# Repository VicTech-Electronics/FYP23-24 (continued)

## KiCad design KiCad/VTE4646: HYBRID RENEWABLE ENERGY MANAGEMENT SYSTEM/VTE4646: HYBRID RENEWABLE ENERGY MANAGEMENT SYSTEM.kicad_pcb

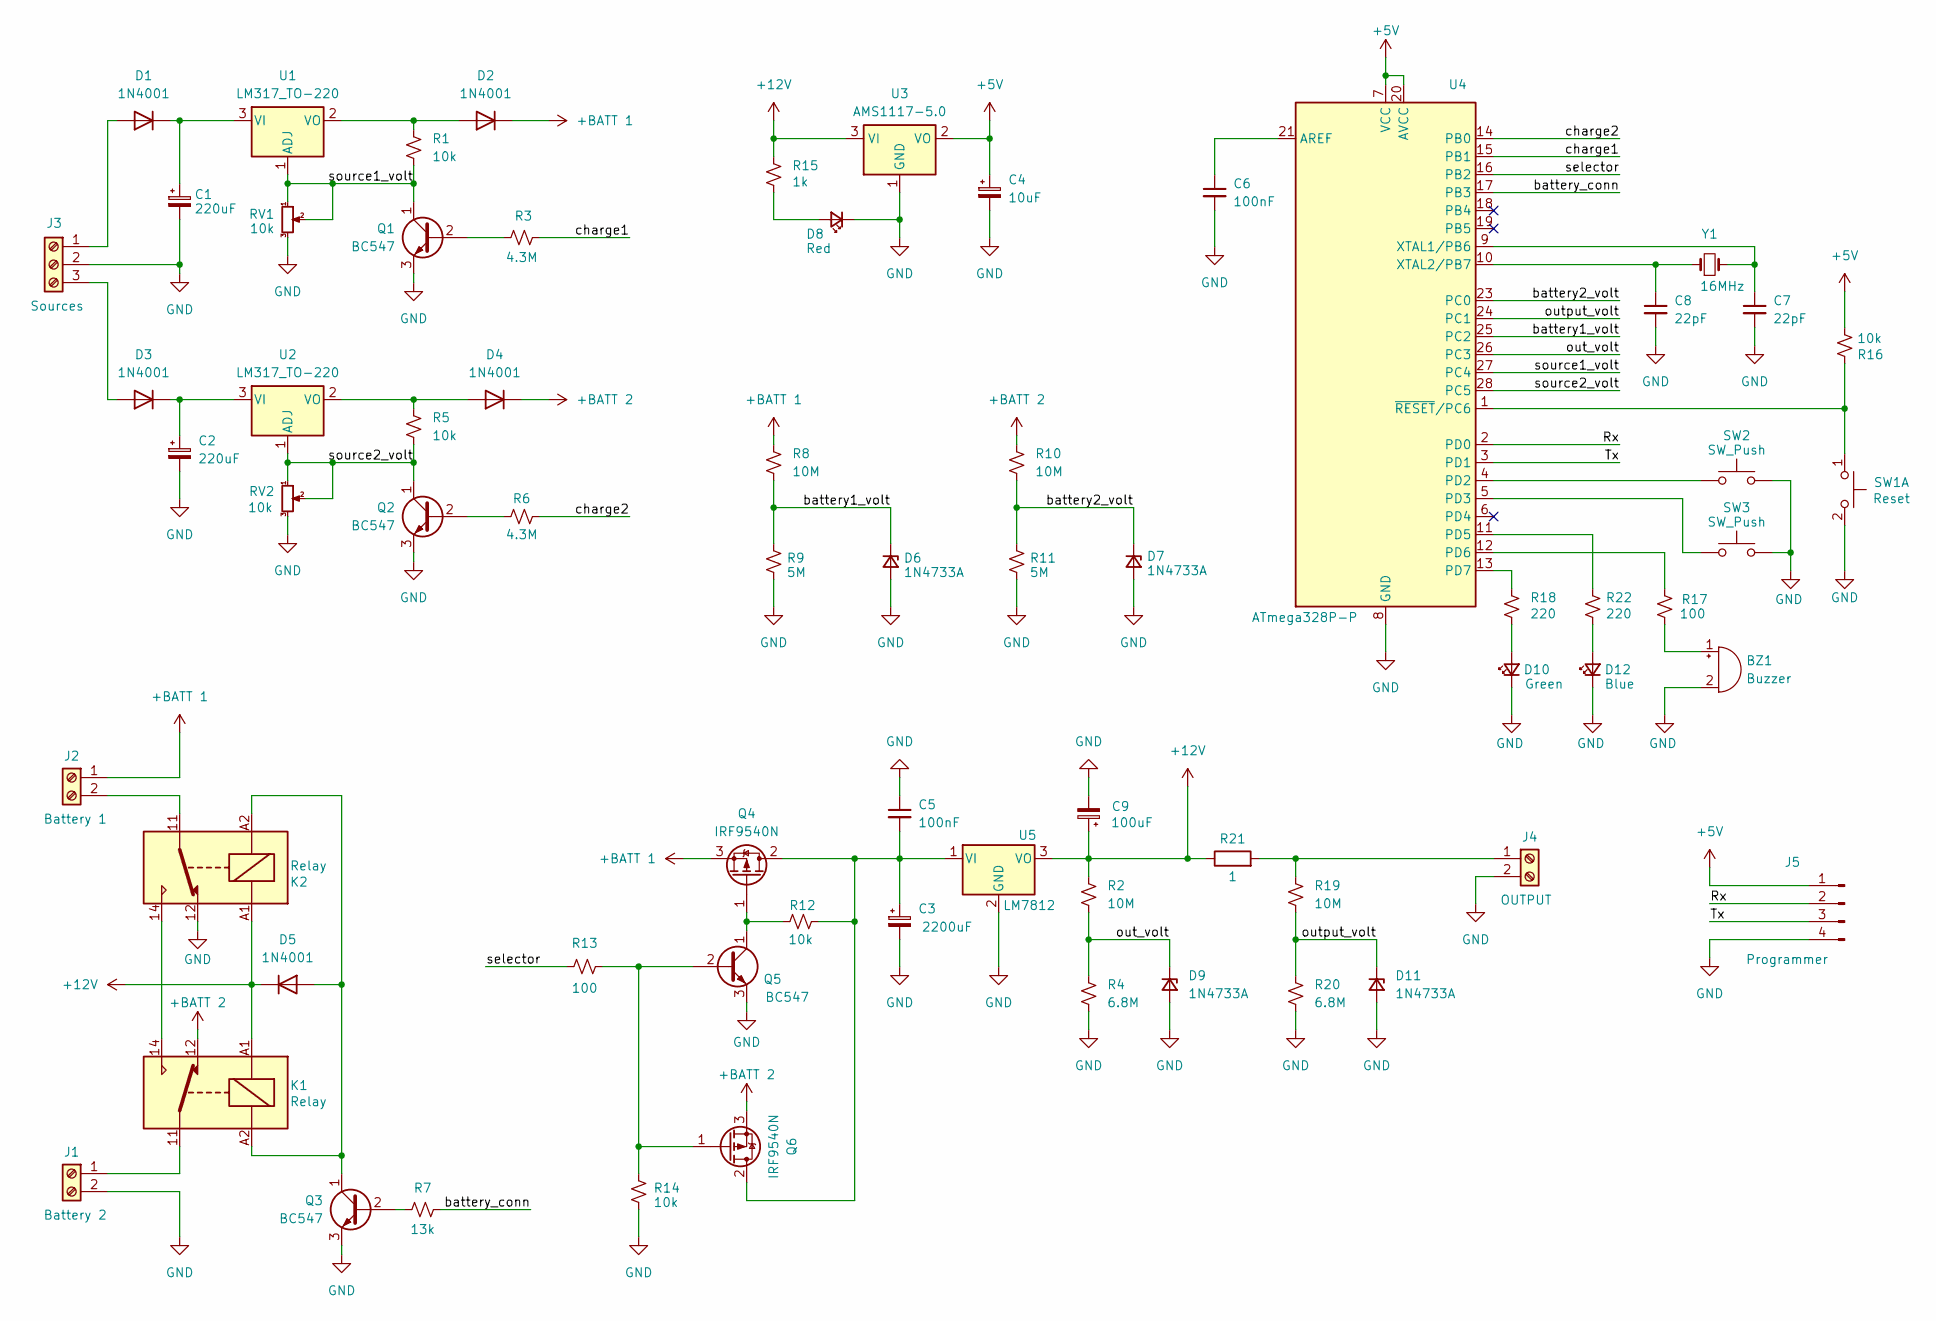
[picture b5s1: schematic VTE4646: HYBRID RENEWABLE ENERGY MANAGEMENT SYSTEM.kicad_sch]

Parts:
BZ1: Buzzer; Buzzer_12x9.5RM7.6
C1, C2: 220uF; CP_Radial_D6.3mm_P2.50mm
C3: 2200uF; CP_Radial_D6.3mm_P2.50mm
C4: 10uF; CP_Radial_D6.3mm_P2.50mm
C5, C6: 100nF; C_Disc_D3.0mm_W1.6mm_P2.50mm
C7, C8: 22pF; C_Disc_D3.0mm_W1.6mm_P2.50mm
C9: 100uF; CP_Radial_D6.3mm_P2.50mm
D1, D2, D3, D4, D5: 1N4001; D_DO-41_SOD81_P10.16mm_Horizontal
D6, D7, D9, D11: 1N4733A; D_A-405_P10.16mm_Horizontal
D8: Red; LED_D3.0mm_Clear
D10: Green; LED_D3.0mm_Clear
D12: Blue; LED_D3.0mm_Clear
J1: Battery 2; TerminalBlock_bornier-2_P5.08mm
J2: Battery 1; TerminalBlock_bornier-2_P5.08mm
J3: Sources; TerminalBlock_bornier-3_P5.08mm
J4: OUTPUT; TerminalBlock_bornier-2_P5.08mm
J5: Programmer; PinHeader_1x04_P2.54mm_Vertical
K1, K2: Relay; Relay_SPDT_Finder_36.11
Q1, Q2, Q3, Q5: BC547; TO-92_Inline
Q4, Q6: IRF9540N; TO-220-3_Vertical
R1, R5, R12, R14, R16: 10k; R_Axial_DIN0207_L6.3mm_D2.5mm_P10.16mm_Horizontal
R2, R8, R10, R19: 10M; R_Axial_DIN0207_L6.3mm_D2.5mm_P10.16mm_Horizontal
R3, R6: 4.3M; R_Axial_DIN0207_L6.3mm_D2.5mm_P10.16mm_Horizontal
R4, R20: 6.8M; R_Axial_DIN0207_L6.3mm_D2.5mm_P10.16mm_Horizontal
R7: 13k; R_Axial_DIN0207_L6.3mm_D2.5mm_P10.16mm_Horizontal
R9, R11: 5M; R_Axial_DIN0207_L6.3mm_D2.5mm_P10.16mm_Horizontal
R13, R17: 100; R_Axial_DIN0207_L6.3mm_D2.5mm_P10.16mm_Horizontal
R15: 1k; R_Axial_DIN0207_L6.3mm_D2.5mm_P10.16mm_Horizontal
R18, R22: 220; R_Axial_DIN0207_L6.3mm_D2.5mm_P10.16mm_Horizontal
R21: 1; R_Axial_Power_L20.0mm_W6.4mm_P30.48mm
RV1, RV2: 10k; Potentiometer_Runtron_RM-065_Vertical
SW1: Reset; SW_PUSH_6mm_H4.3mm
SW2, SW3: SW_Push; PinHeader_2x01_P2.00mm_Vertical
U1, U2: LM317_TO-220; TO-220-3_Vertical
U3: AMS1117-5.0; SOT-223-3_TabPin2
U4: ATmega328P-P; DIP-28_W7.62mm
U5: LM7812; TO-220-3_Vertical
Y1: 16MHz; Crystal_HC18-U_Vertical

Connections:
+5V: C4.1, J5.1, R16.2, U3.2 (VO), U4.7 (VCC), U4.20 (AVCC)
+12V: C9.1, D5.1 (K), K1.A1, K2.A1, R2.1, R15.1, R21.1, U3.3 (VI), U5.3 (VO)
+BATT 1: D2.1 (K), J2.1, Q4.3 (S), R8.1
+BATT 2: D4.1 (K), K1.12, Q6.3 (S), R10.1
/Rx: J5.2, U4.2 (PD0)
/Tx: J5.3, U4.3 (PD1)
/battery1_volt: D6.1 (K), R8.2, R9.1, U4.25 (PC2)
/battery2_volt: D7.1 (K), R10.2, R11.1, U4.23 (PC0)
/battery_conn: R7.2, U4.17 (PB3)
/charge1: R3.2, U4.15 (PB1)
/charge2: R6.2, U4.14 (PB0)
/out_volt: D9.1 (K), R2.2, R4.1, U4.26 (PC3)
/output_volt: D11.1 (K), R19.2, R20.1, U4.24 (PC1)
/selector: R13.1, U4.16 (PB2)
/source1_volt: Q1.1 (C), R1.2, RV1.1, RV1.2, U1.1 (ADJ), U4.27 (PC4)
/source2_volt: Q2.1 (C), R5.2, RV2.1, RV2.2, U2.1 (ADJ), U4.28 (PC5)
GND: BZ1.2 (-), C1.2, C2.2, C3.2, C4.2, C5.1, C6.2, C7.2, C8.2, C9.2, D6.2 (A), D7.2 (A), D8.1 (K), D9.2 (A), D10.1 (K), D11.2 (A), D12.1 (K), J1.2, J3.2, J4.2, J5.4, K2.12, Q1.3 (E), Q2.3 (E), Q3.3 (E), Q5.3 (E), R4.2, R9.2, R11.2, R14.2, R20.2, RV1.3, RV2.3, SW1.2 (D), SW2.2, SW3.2, U3.1 (GND), U4.8 (GND), U4.22 (GND), U5.2 (GND)
unnamed: BZ1.1 (+), R17.2
unnamed: D1.2 (A), J3.1
unnamed: C1.1, D1.1 (K), U1.3 (VI)
unnamed: D2.2 (A), R1.1, U1.2 (VO)
unnamed: D3.2 (A), J3.3
unnamed: C2.1, D3.1 (K), U2.3 (VI)
unnamed: D4.2 (A), R5.1, U2.2 (VO)
unnamed: D5.2 (A), K1.A2, K2.A2, Q3.1 (C)
unnamed: D8.2 (A), R15.2
unnamed: D10.2 (A), R18.2
unnamed: D12.2 (A), R22.2
unnamed: J1.1, K1.11
unnamed: J2.2, K2.11
unnamed: J4.1, R19.1, R21.2
unnamed: K1.14, K2.14
unnamed: Q1.2 (B), R3.1
unnamed: Q2.2 (B), R6.1
unnamed: Q3.2 (B), R7.1
unnamed: C3.1, C5.2, Q4.2 (D), Q6.2 (D), R12.2, U5.1 (VI)
unnamed: Q4.1 (G), Q5.1 (C), R12.1
unnamed: Q5.2 (B), Q6.1 (G), R13.2, R14.1
unnamed: R16.1, SW1.1 (C), U4.1 (~RESET/PC6)
unnamed: C6.1, U4.21 (AREF)
unnamed: SW2.1, U4.4 (PD2)
unnamed: SW3.1, U4.5 (PD3)
unnamed: R22.1, U4.11 (PD5)
unnamed: R17.1, U4.12 (PD6)
unnamed: R18.1, U4.13 (PD7)
unnamed: C7.1, U4.9 (XTAL1/PB6), Y1.2
unnamed: C8.1, U4.10 (XTAL2/PB7), Y1.1

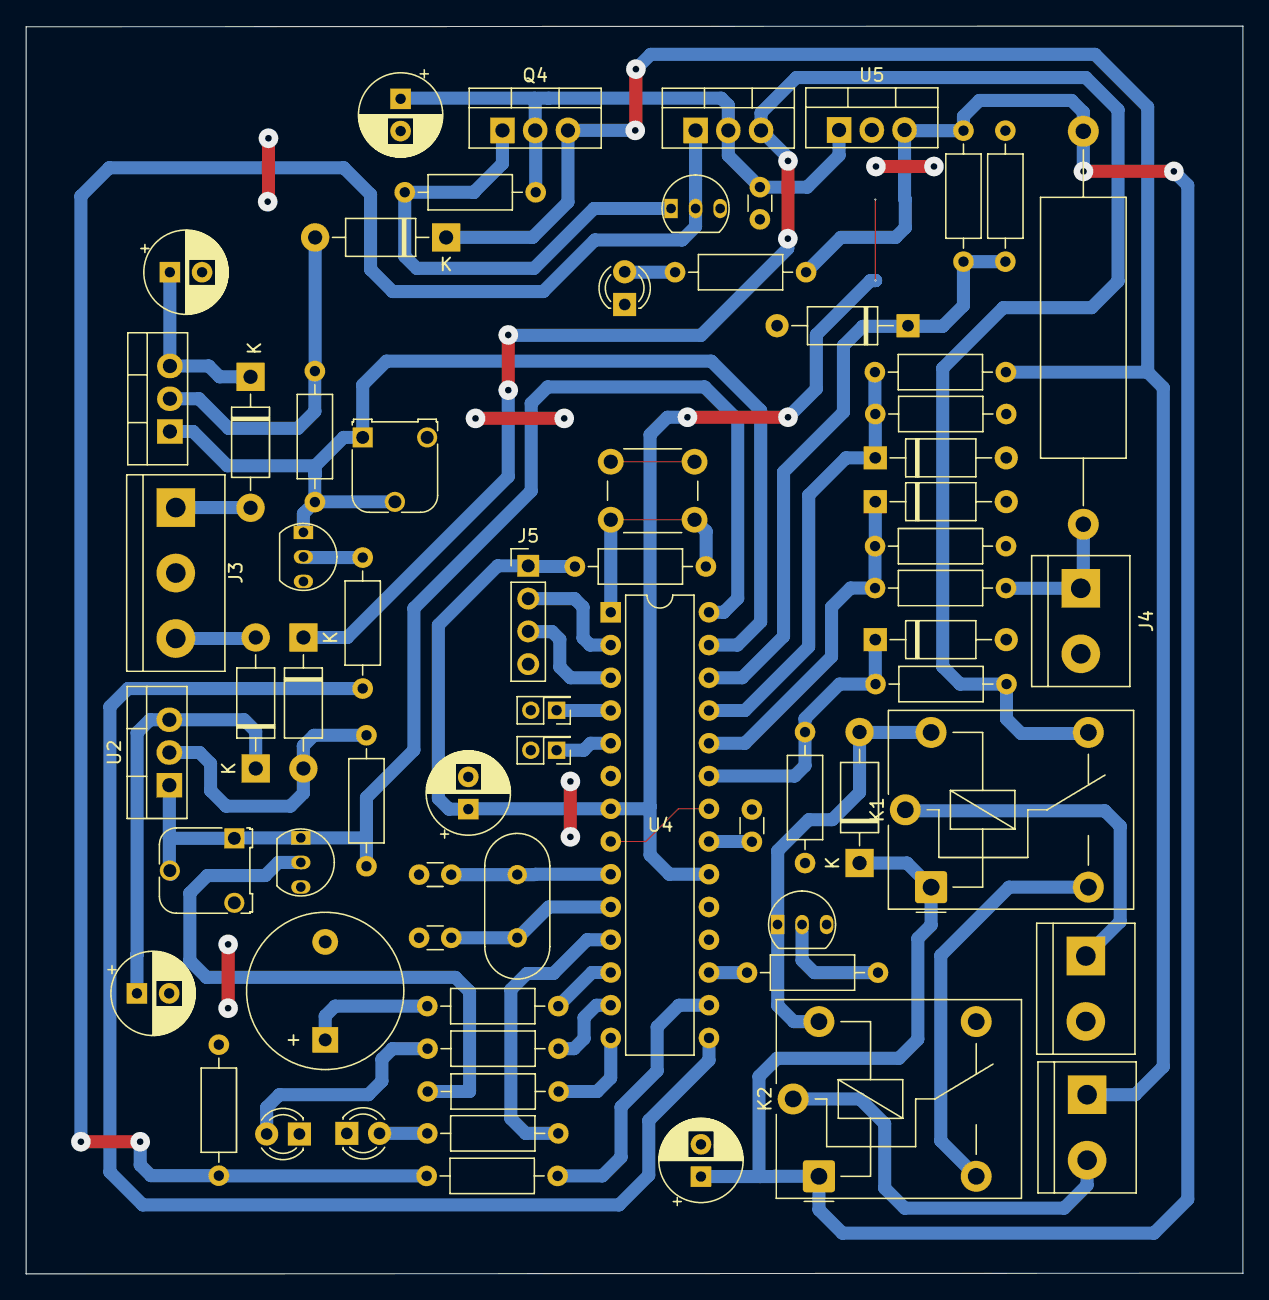
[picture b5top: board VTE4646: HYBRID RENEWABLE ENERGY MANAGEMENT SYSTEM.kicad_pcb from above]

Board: 2 copper layers, 94.4 x 96.8 mm, 68 parts (1 on the bottom side), 47 nets.

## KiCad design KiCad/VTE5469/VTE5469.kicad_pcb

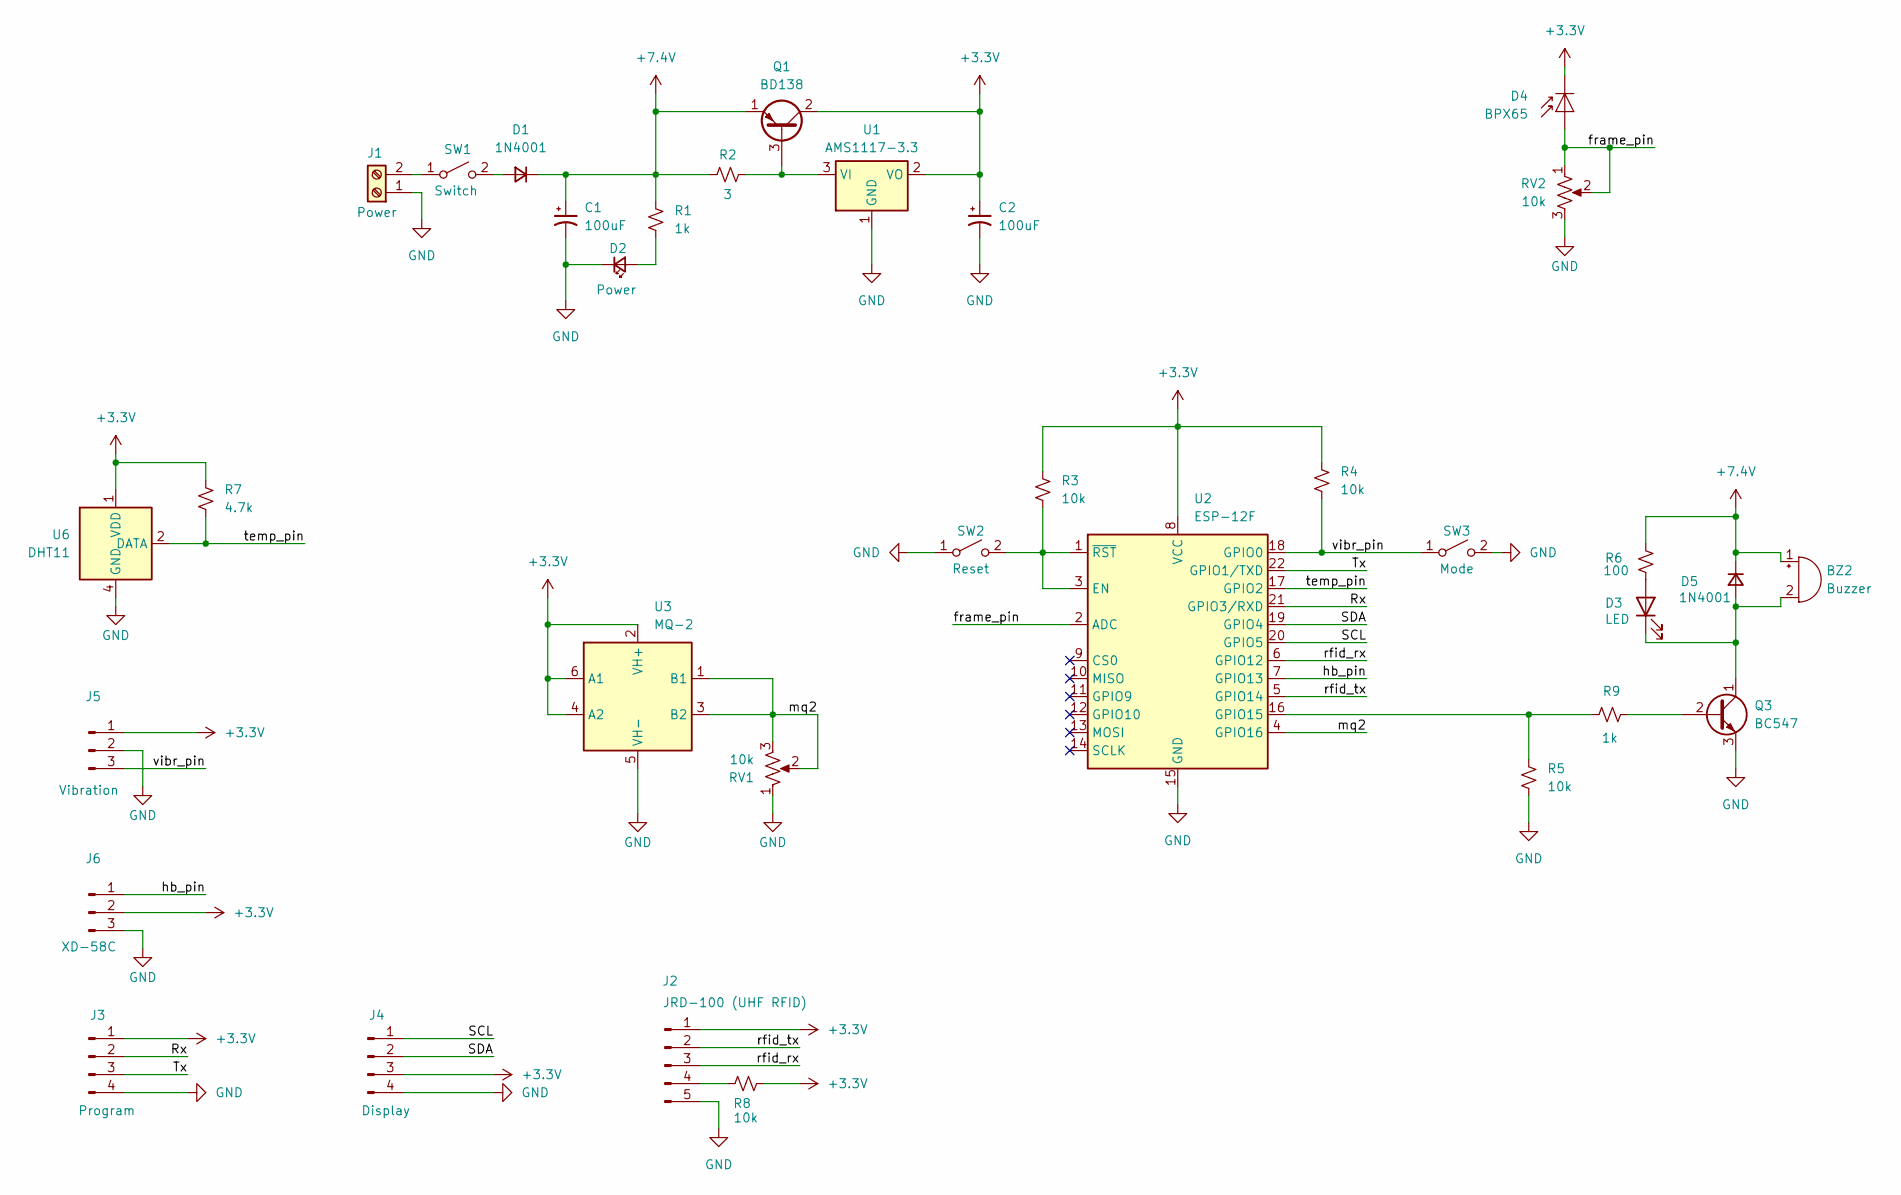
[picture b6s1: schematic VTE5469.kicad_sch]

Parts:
BZ2: Buzzer; PinHeader_1x02_P2.54mm_Vertical
C1, C2: 100uF; CP_Radial_D5.0mm_P2.50mm
D1, D5: 1N4001; D_A-405_P10.16mm_Horizontal
D2: Power; LED_D3.0mm
D3: LED; LED_D3.0mm
D4: BPX65; TO-18-2_Lens
J1: Power; TerminalBlock_bornier-2_P5.08mm
J2: JRD-100 (UHF RFID); PinHeader_1x05_P2.54mm_Vertical
J3: Program; PinHeader_1x04_P2.54mm_Vertical
J4: Display; PinHeader_1x04_P2.54mm_Vertical
J5: Vibration; PinHeader_1x03_P2.54mm_Vertical
J6: XD-58C; PinHeader_1x03_P2.54mm_Vertical
Q1: BD138; TO-126-3_Vertical
Q3: BC547; TO-92_Inline
R1, R9: 1k; R_Axial_DIN0207_L6.3mm_D2.5mm_P10.16mm_Horizontal
R2: 3; R_Axial_DIN0207_L6.3mm_D2.5mm_P10.16mm_Horizontal
R3, R4, R5, R8: 10k; R_Axial_DIN0207_L6.3mm_D2.5mm_P10.16mm_Horizontal
R6: 100; R_Axial_DIN0207_L6.3mm_D2.5mm_P10.16mm_Horizontal
R7: 4.7k; R_Axial_DIN0207_L6.3mm_D2.5mm_P10.16mm_Horizontal
RV1, RV2: 10k; Potentiometer_Runtron_RM-065_Vertical
SW1: Switch; TestPoint_2Pads_Pitch2.54mm_Drill0.8mm
SW2: Reset; SW_PUSH_6mm
SW3: Mode; SW_PUSH_6mm
U1: AMS1117-3.3; SOT-223-3_TabPin2
U2: ESP-12F; ESP-12E
U3: MQ-2; MQ-6
U6: DHT11; Aosong_DHT11_5.5x12.0_P2.54mm

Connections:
+3.3V: C2.1, D4.1 (K), J2.1, J3.1, J4.3, J5.1, J6.2, Q1.2 (C), R3.1, R4.1, R7.1, R8.2, U1.2 (VO), U2.8 (VCC), U3.2 (VH+), U3.4 (A2), U3.6 (A1), U6.1 (VDD)
+7.4V: BZ2.1 (+), C1.1, D1.1 (K), D5.1 (K), Q1.1 (E), R1.1, R2.1, R6.1
/Rx: J3.2, U2.21 (GPIO3/RXD)
/SCL: J4.1, U2.20 (GPIO5)
/SDA: J4.2, U2.19 (GPIO4)
/Tx: J3.3, U2.22 (GPIO1/TXD)
/frame_pin: D4.2 (A), RV2.1, RV2.2, U2.2 (ADC)
/hb_pin: J6.1, U2.7 (GPIO13)
/mq2: RV1.2, RV1.3, U2.4 (GPIO16), U3.1 (B1), U3.3 (B2)
/rfid_rx: J2.3, U2.6 (GPIO12)
/rfid_tx: J2.2, U2.5 (GPIO14)
/temp_pin: R7.2, U2.17 (GPIO2), U6.2 (DATA)
/vibr_pin: J5.3, R4.2, SW3.1 (A), U2.18 (GPIO0)
GND: C1.2, C2.2, D2.1 (K), J1.1, J2.5, J3.4, J4.4, J5.2, J6.3, Q3.3 (E), R5.2, RV1.1, RV2.3, SW2.1 (A), SW3.2 (B), U1.1 (GND), U2.15 (GND), U3.5 (VH-), U6.4 (GND)
unnamed: BZ2.2 (-), D3.1 (K), D5.2 (A), Q3.1 (C)
unnamed: D1.2 (A), SW1.2 (B)
unnamed: D2.2 (A), R1.2
unnamed: D3.2 (A), R6.2
unnamed: J1.2, SW1.1 (A)
unnamed: J2.4, R8.1
unnamed: Q1.3 (B), R2.2, U1.3 (VI)
unnamed: Q3.2 (B), R9.2
unnamed: R3.2, SW2.2 (B), U2.1 (~RST), U2.3 (EN)
unnamed: R5.1, R9.1, U2.16 (GPIO15)

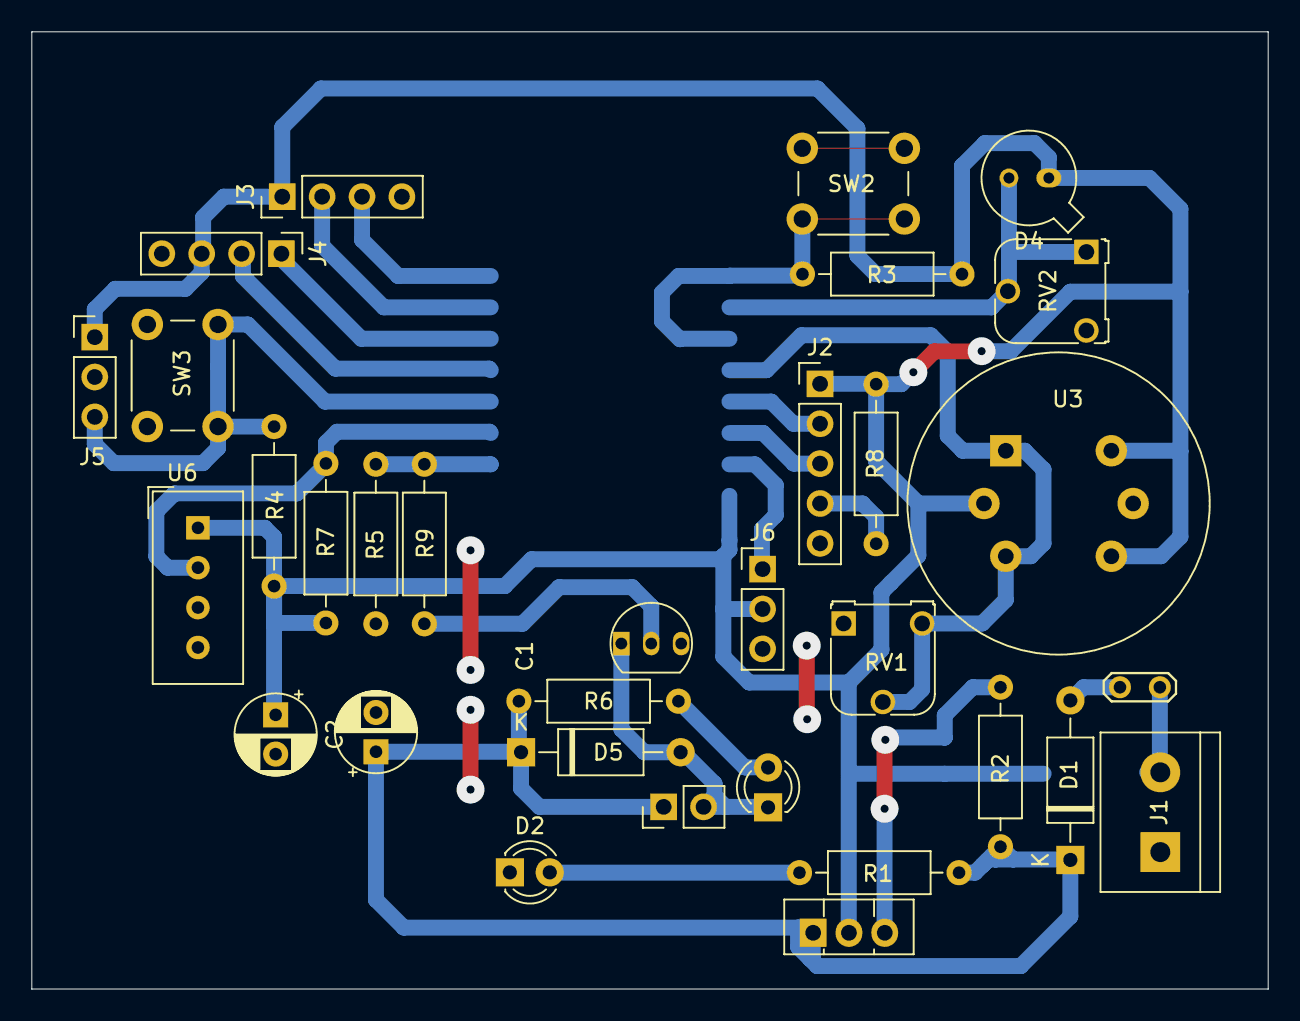
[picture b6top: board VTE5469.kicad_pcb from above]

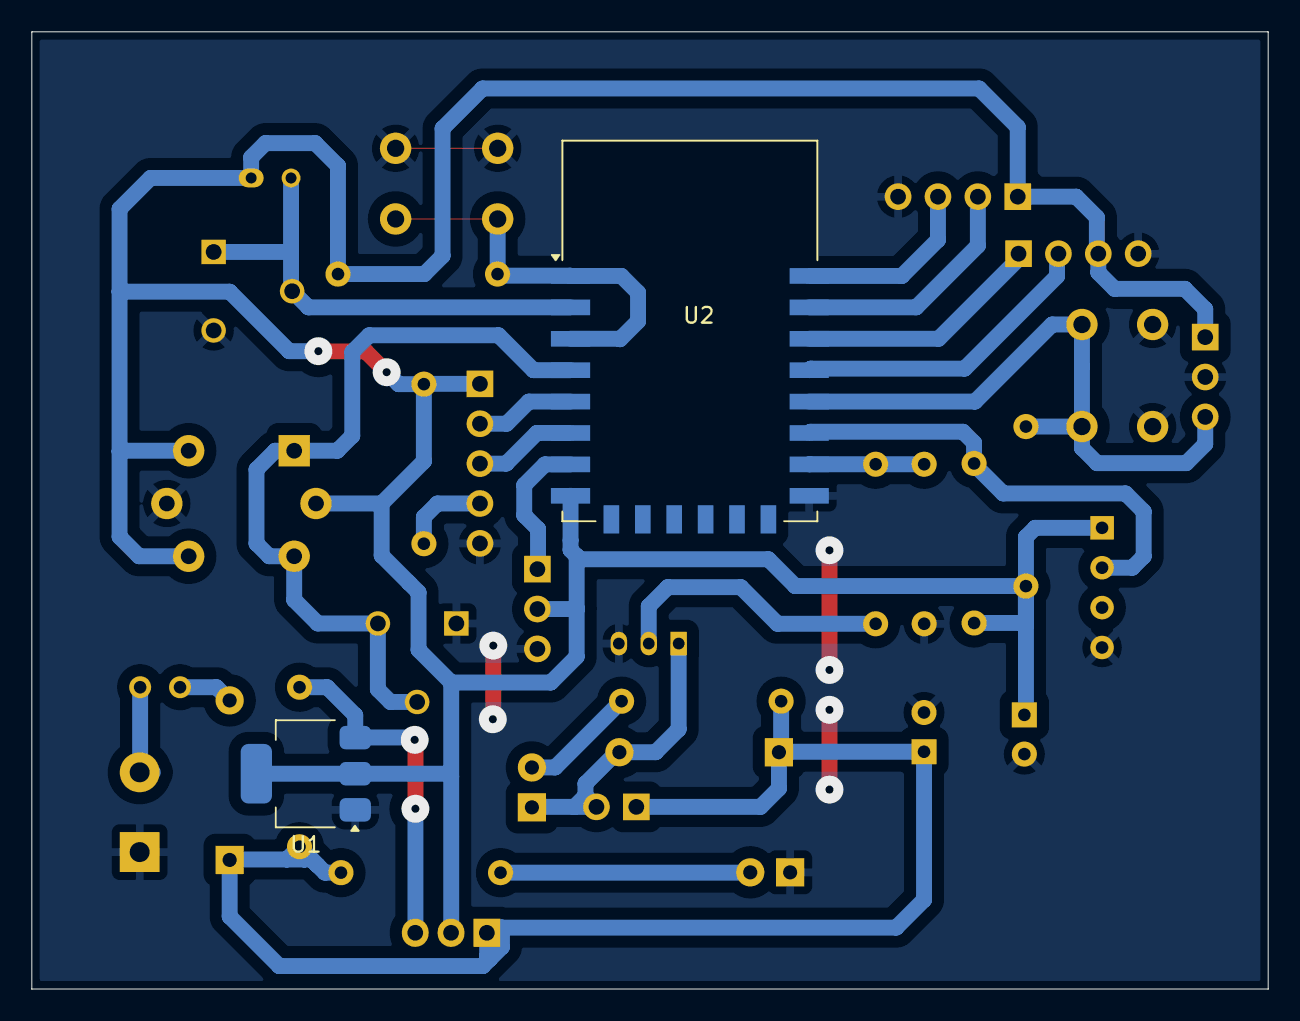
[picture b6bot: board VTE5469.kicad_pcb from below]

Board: 2 copper layers, 78.7 x 61.0 mm, 34 parts (2 on the bottom side), 24 nets.

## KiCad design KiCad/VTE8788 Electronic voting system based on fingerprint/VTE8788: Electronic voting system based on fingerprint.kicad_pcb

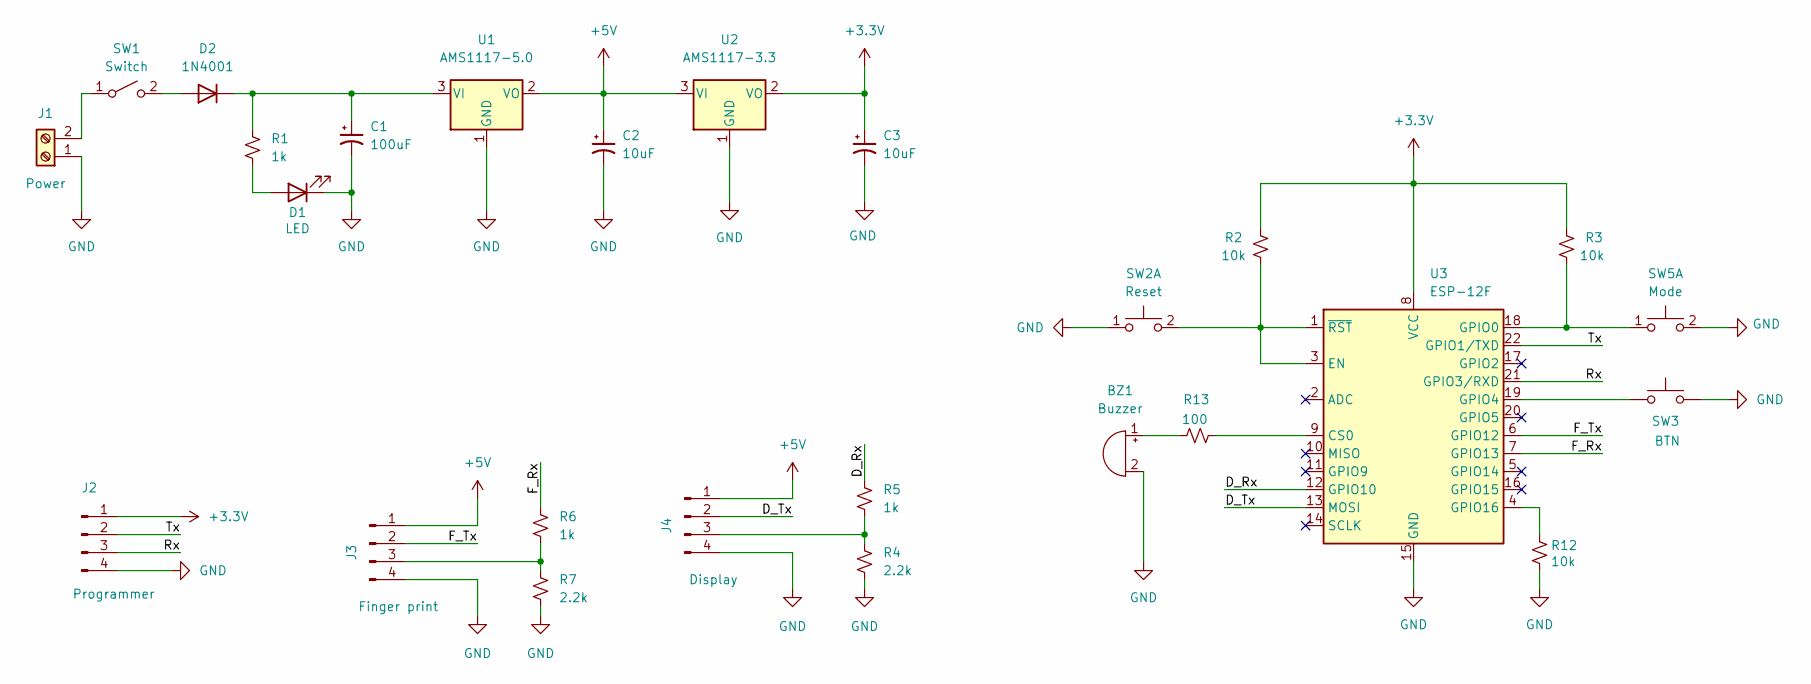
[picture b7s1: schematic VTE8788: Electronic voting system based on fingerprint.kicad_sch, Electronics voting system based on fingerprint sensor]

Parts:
BZ1: Buzzer; Buzzer_12x9.5RM7.6
C1: 100uF; CP_Radial_D4.0mm_P2.00mm
C2, C3: 10uF; CP_Radial_D4.0mm_P2.00mm
D1: LED; LED_D3.0mm
D2: 1N4001; D_DO-41_SOD81_P10.16mm_Horizontal
J1: Power; TerminalBlock_bornier-2_P5.08mm
J2: Programmer; PinHeader_1x04_P2.54mm_Vertical
J3: Finger print; PinHeader_1x04_P2.54mm_Vertical
J4: Display; PinHeader_1x04_P2.54mm_Vertical
R1, R5, R6: 1k; R_Axial_DIN0207_L6.3mm_D2.5mm_P10.16mm_Horizontal
R2, R3, R12: 10k; R_Axial_DIN0207_L6.3mm_D2.5mm_P10.16mm_Horizontal
R4, R7: 2.2k; R_Axial_DIN0207_L6.3mm_D2.5mm_P10.16mm_Horizontal
R13: 100; R_Axial_DIN0207_L6.3mm_D2.5mm_P10.16mm_Horizontal
SW1: Switch; TestPoint_2Pads_Pitch2.54mm_Drill0.8mm
SW2: Reset; SW_PUSH_6mm
SW3: BTN; TestPoint_2Pads_Pitch2.54mm_Drill0.8mm
SW5: Mode; SW_PUSH_6mm
U1: AMS1117-5.0; SOT-223-3_TabPin2
U2: AMS1117-3.3; SOT-223-3_TabPin2
U3: ESP-12F; ESP-12E

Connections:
+3.3V: C3.1, J2.1, R2.2, R3.1, U2.2 (VO), U3.8 (VCC)
+5V: C2.1, J3.1, J4.1, U1.2 (VO), U2.3 (VI)
/D_Rx: R5.1, U3.12 (GPIO10)
/D_Tx: J4.2, U3.13 (MOSI)
/F_Rx: R6.1, U3.7 (GPIO13)
/F_Tx: J3.2, U3.6 (GPIO12)
/Rx: J2.3, U3.21 (GPIO3/RXD)
/Tx: J2.2, U3.22 (GPIO1/TXD)
GND: BZ1.2 (+), C1.2, C2.2, C3.2, D1.1 (K), J1.1, J2.4, J3.4, J4.4, R4.2, R7.2, R12.2, SW2.1 (C), SW3.2, SW5.2 (D), U1.1 (GND), U2.1 (GND), U3.15 (GND)
unnamed: BZ1.1 (-), R13.1
unnamed: D1.2 (A), R1.2
unnamed: D2.2 (A), SW1.2 (B)
unnamed: C1.1, D2.1 (K), R1.1, U1.3 (VI)
unnamed: J1.2, SW1.1 (A)
unnamed: J3.3, R6.2, R7.1
unnamed: J4.3, R4.1, R5.2
unnamed: R2.1, SW2.2 (D), U3.1 (~RST), U3.3 (EN)
unnamed: R3.2, SW5.1 (C), U3.18 (GPIO0)
unnamed: R13.2, U3.9 (CS0)
unnamed: SW3.1, U3.19 (GPIO4)
unnamed: R12.1, U3.4 (GPIO16)

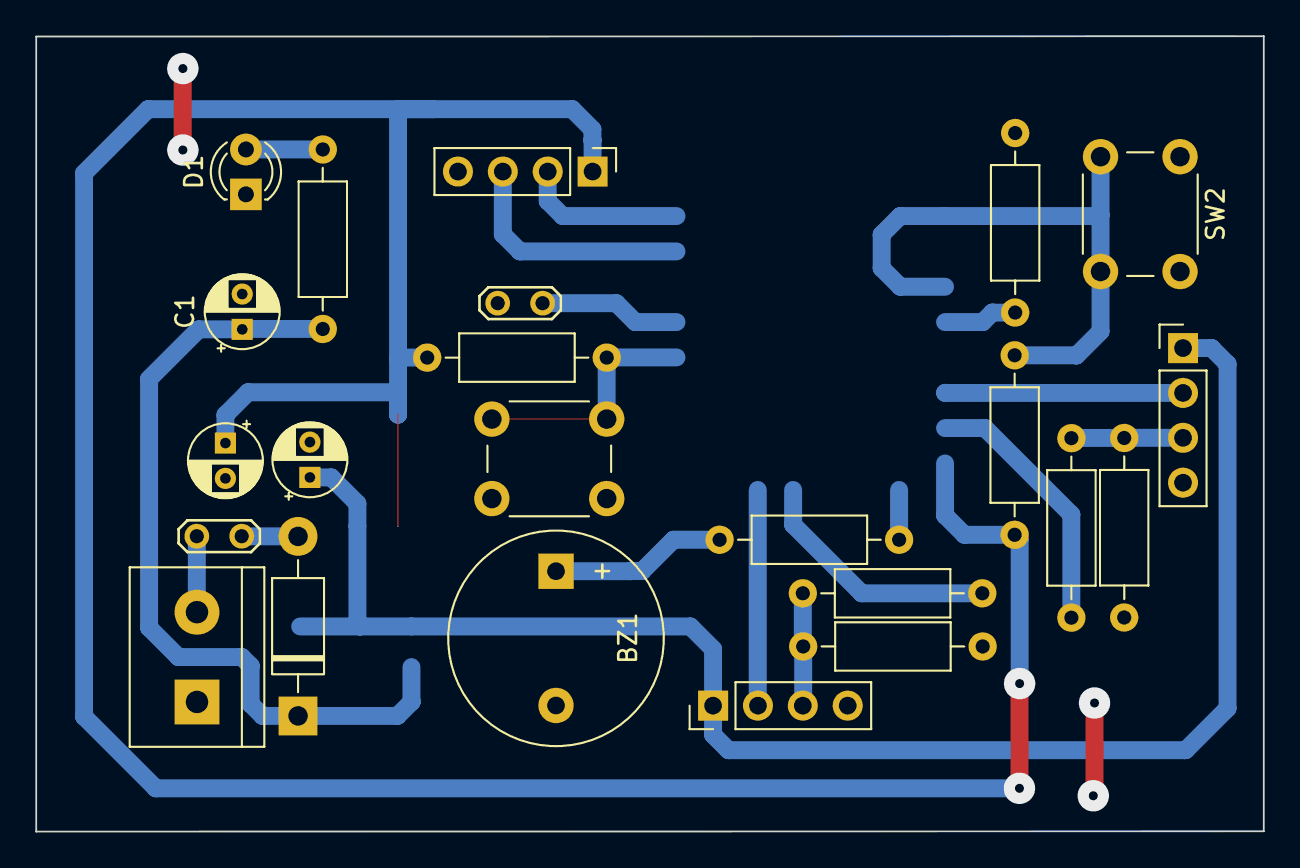
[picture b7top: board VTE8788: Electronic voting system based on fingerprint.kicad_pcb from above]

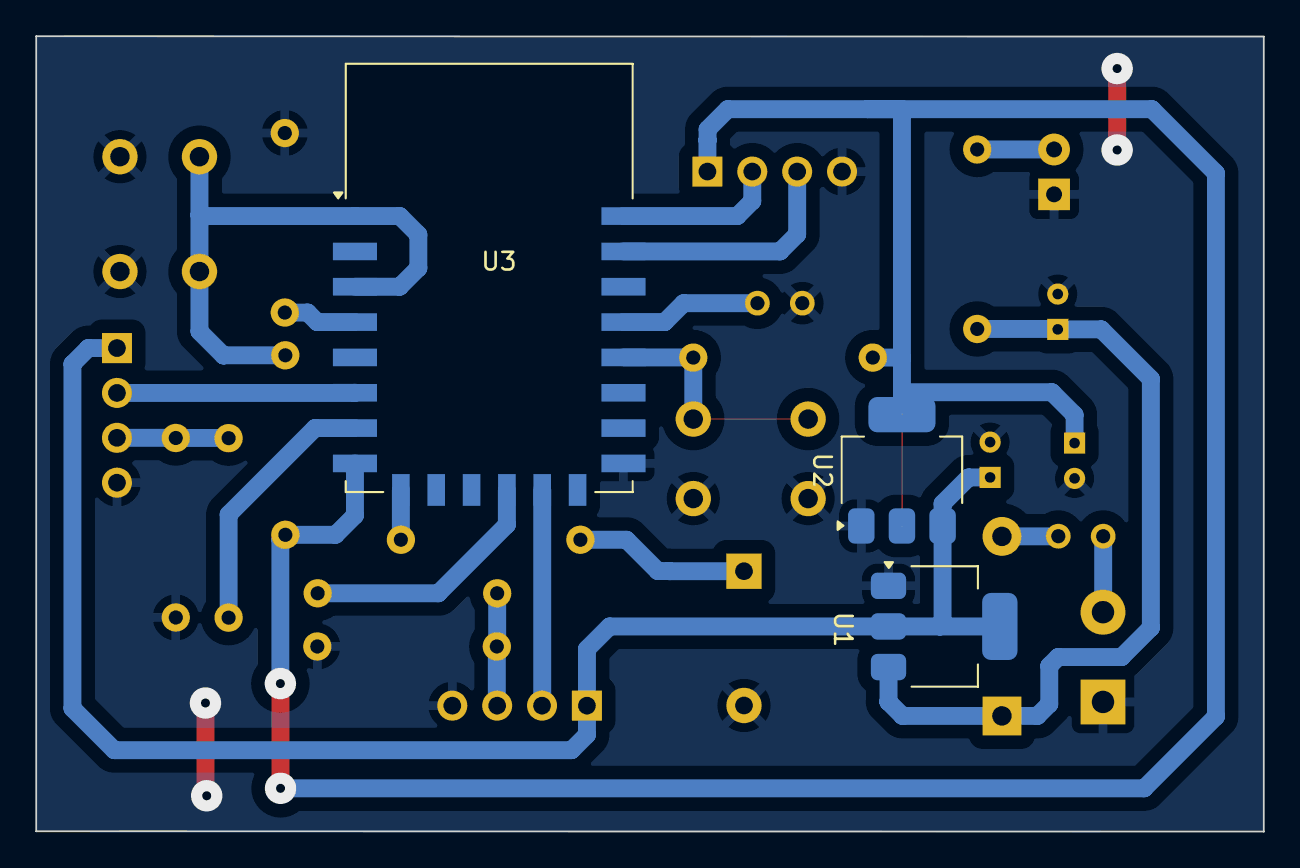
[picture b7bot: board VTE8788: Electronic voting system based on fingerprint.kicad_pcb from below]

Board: 2 copper layers, 69.5 x 45.0 mm, 26 parts (3 on the bottom side), 21 nets.

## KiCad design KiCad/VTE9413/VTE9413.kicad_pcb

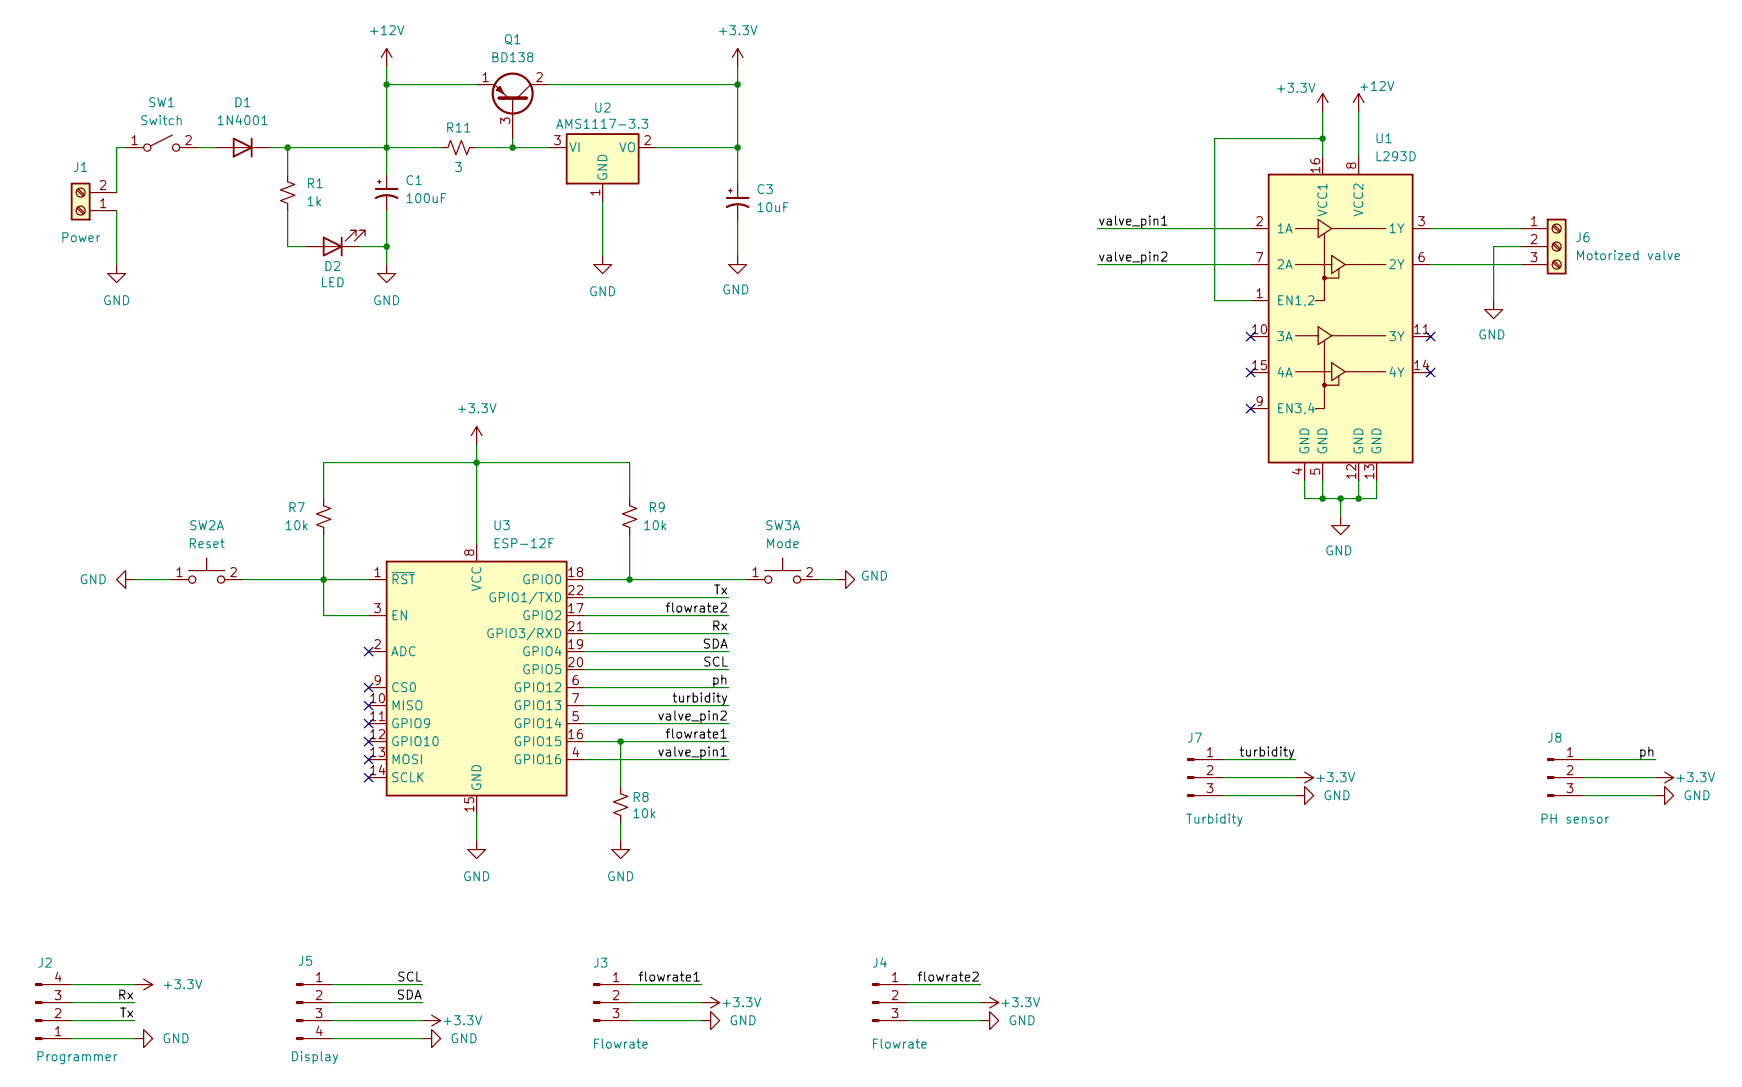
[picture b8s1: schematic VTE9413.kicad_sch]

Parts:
C1: 100uF; CP_Radial_D4.0mm_P2.00mm
C3: 10uF; CP_Radial_D4.0mm_P2.00mm
D1: 1N4001; D_DO-41_SOD81_P10.16mm_Horizontal
D2: LED; LED_D3.0mm
J1: Power; TerminalBlock_bornier-2_P5.08mm
J2: Programmer; PinHeader_1x04_P2.54mm_Vertical
J3, J4: Flowrate; PinHeader_1x03_P2.54mm_Vertical
J5: Display; PinHeader_1x04_P2.54mm_Vertical
J6: Motorized valve; TerminalBlock_bornier-3_P5.08mm
J7: Turbidity; PinHeader_1x03_P2.54mm_Vertical
J8: PH sensor; PinHeader_1x03_P2.54mm_Vertical
Q1: BD138; TO-126-3_Vertical
R1: 1k; R_Axial_DIN0207_L6.3mm_D2.5mm_P10.16mm_Horizontal
R7, R8, R9: 10k; R_Axial_DIN0207_L6.3mm_D2.5mm_P10.16mm_Horizontal
R11: 3; R_Axial_DIN0207_L6.3mm_D2.5mm_P10.16mm_Horizontal
SW1: Switch; TestPoint_2Pads_Pitch2.54mm_Drill0.8mm
SW2: Reset; SW_PUSH_6mm
SW3: Mode; SW_PUSH_6mm
U1: L293D; DIP-16_W7.62mm
U2: AMS1117-3.3; SOT-223-3_TabPin2
U3: ESP-12F; ESP-12E

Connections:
+3.3V: C3.1, J2.4, J3.2, J4.2, J5.3, J7.2, J8.2, Q1.2 (C), R7.2, R9.1, U1.1 (EN1,2), U1.16 (VCC1), U2.2 (VO), U3.8 (VCC)
+12V: C1.1, D1.1 (K), Q1.1 (E), R1.1, R11.1, U1.8 (VCC2)
/Rx: J2.3, U3.21 (GPIO3/RXD)
/SCL: J5.1, U3.20 (GPIO5)
/SDA: J5.2, U3.19 (GPIO4)
/Tx: J2.2, U3.22 (GPIO1/TXD)
/flowrate1: J3.1, R8.1, U3.16 (GPIO15)
/flowrate2: J4.1, U3.17 (GPIO2)
/ph: J8.1, U3.6 (GPIO12)
/turbidity: J7.1, U3.7 (GPIO13)
/valve_pin1: U1.2 (1A), U3.4 (GPIO16)
/valve_pin2: U1.7 (2A), U3.5 (GPIO14)
GND: C1.2, C3.2, D2.1 (K), J1.1, J2.1, J3.3, J4.3, J5.4, J6.2, J7.3, J8.3, R8.2, SW2.1 (C), SW3.2 (D), U1.4 (GND), U1.5 (GND), U1.12 (GND), U1.13 (GND), U2.1 (GND), U3.15 (GND)
unnamed: D1.2 (A), SW1.2 (B)
unnamed: D2.2 (A), R1.2
unnamed: J1.2, SW1.1 (A)
unnamed: J6.1, U1.3 (1Y)
unnamed: J6.3, U1.6 (2Y)
unnamed: Q1.3 (B), R11.2, U2.3 (VI)
unnamed: R7.1, SW2.2 (D), U3.1 (~RST), U3.3 (EN)
unnamed: R9.2, SW3.1 (C), U3.18 (GPIO0)
